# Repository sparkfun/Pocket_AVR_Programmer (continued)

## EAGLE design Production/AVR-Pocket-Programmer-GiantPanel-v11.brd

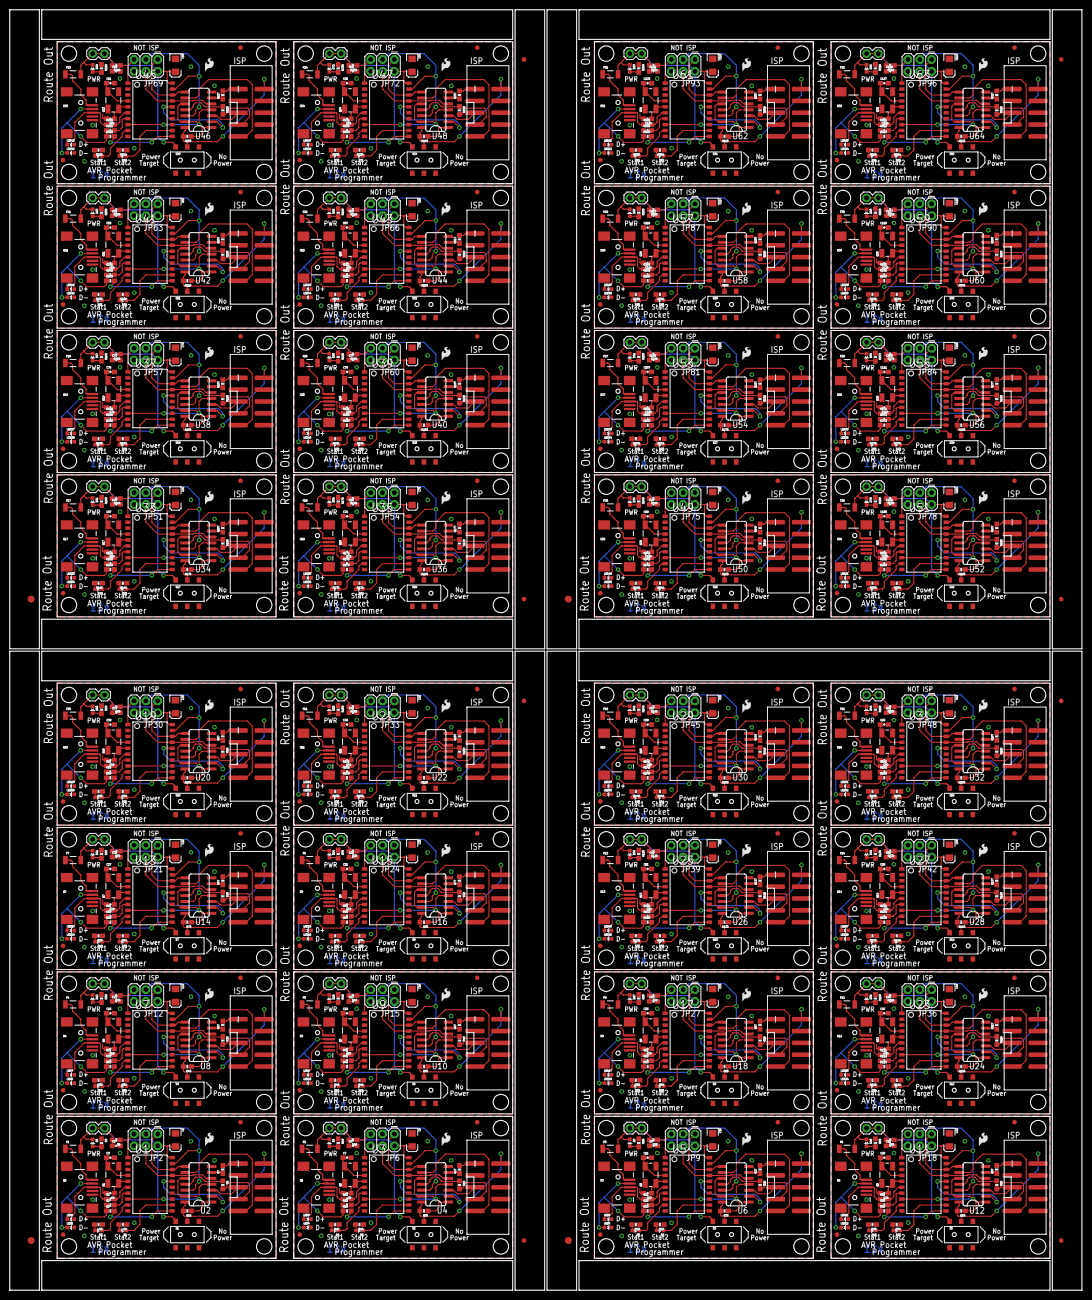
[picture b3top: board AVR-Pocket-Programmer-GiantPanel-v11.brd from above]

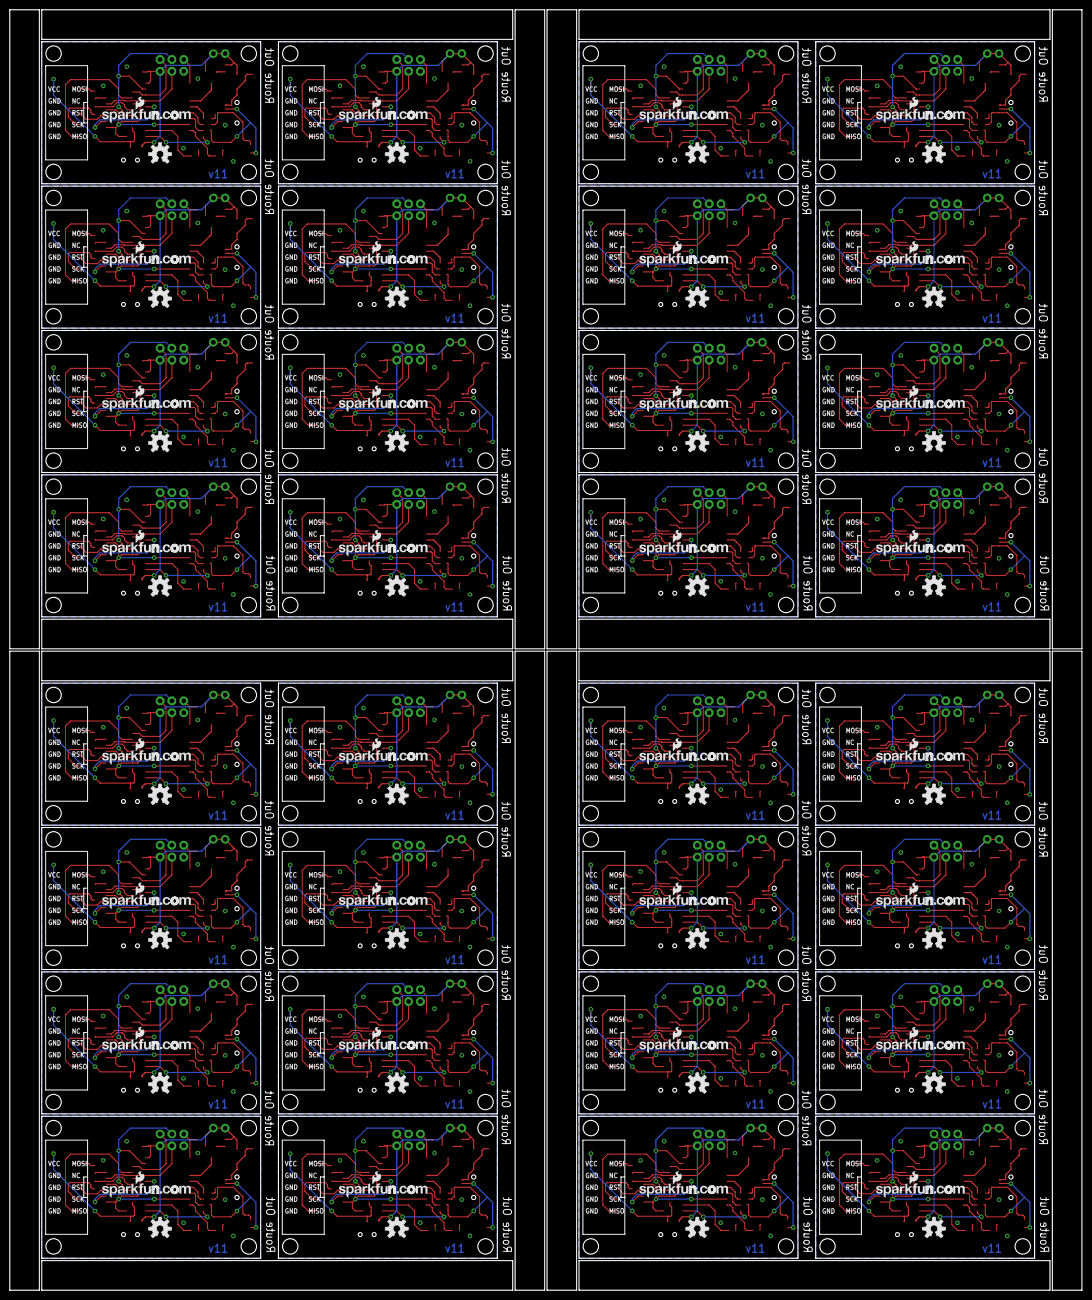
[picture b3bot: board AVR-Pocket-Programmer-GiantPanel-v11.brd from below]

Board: 2 copper layers, 230.1 x 274.8 mm, 1196 parts (64 on the bottom side), 896 nets.

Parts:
C1, C6, C10, C14, C18, C22, C26, C30, C34, C38, C42, C46, C50, C54, C58, C62, C66, C70, C74, C78, C82, C86, C90, C94, C98, C102, C106, C110, C114, C118, C122, C126: 10uF; EIA3216
C2, C5, C9, C13, C17, C21, C25, C29, C33, C37, C41, C45, C49, C53, C57, C61, C65, C69, C73, C77, C81, C85, C89, C93, C97, C101, C105, C109, C113, C117, C121, C125: 0.1uF; 0603-CAP
C3, C4, C7, C8, C11, C12, C15, C16, C19, C20, C23, C24, C27, C28, C31, C32, C35, C36, C39, C40, C43, C44, C47, C48, C51, C52, C55, C56, C59, C60, C63, C64, C67, C68, C71, C72, C75, C76, C79, C80, C83, C84, C87, C88, C91, C92, C95, C96, C99, C100, C103, C104, C107, C108, C111, C112, C115, C116, C119, C120, C123, C124, C127, C128: 22pF; 0603-CAP
D1, D3, D5, D6, D8, D9, D11, D12, D14, D15, D17, D18, D20, D21, D23, D24, D26, D27, D29, D30, D32, D33, D35, D36, D38, D39, D41, D42, D44, D45, D47, D48, D50, D51, D53, D54, D56, D57, D59, D60, D62, D63, D65, D66, D68, D69, D71, D72, D74, D75, D77, D78, D80, D81, D83, D84, D86, D87, D89, D90, D92, D93, D95, D96: Blue; LED-0603
D2, D4, D7, D10, D13, D16, D19, D22, D25, D28, D31, D34, D37, D40, D43, D46, D49, D52, D55, D58, D61, D64, D67, D70, D73, D76, D79, D82, D85, D88, D91, D94: Red; LED-0603
E$1, E$4, E$9, E$12: FIDUCIAL-1.5X3
E$2, E$3, E$5, E$6, E$7, E$8, E$10, E$11: FIDUCIAL-1X2
F1, F2, F3, F4, F5, F6, F7, F8, F9, F10, F11, F12, F13, F14, F15, F16, F17, F18, F19, F20, F21, F22, F23, F24, F25, F26, F27, F28, F29, F30, F31, F32: 500mA; PTC-1206-WIDE
JP1, JP4, JP7, JP10, JP13, JP16, JP19, JP22, JP25, JP28, JP31, JP34, JP37, JP40, JP43, JP46, JP49, JP52, JP55, JP58, JP61, JP64, JP67, JP70, JP73, JP76, JP79, JP82, JP85, JP88, JP91, JP94: Power Select; 1X02
JP2, JP6, JP9, JP12, JP15, JP18, JP21, JP24, JP27, JP30, JP33, JP36, JP39, JP42, JP45, JP48, JP51, JP54, JP57, JP60, JP63, JP66, JP69, JP72, JP75, JP78, JP81, JP84, JP87, JP90, JP93, JP96: AVR_SPI_PRG_6PTH; 2X3
JP3, JP5, JP8, JP11, JP14, JP17, JP20, JP23, JP26, JP29, JP32, JP35, JP38, JP41, JP44, JP47, JP50, JP53, JP56, JP59, JP62, JP65, JP68, JP71, JP74, JP77, JP80, JP83, JP86, JP89, JP92, JP95: AVR_SPI_PROG2SHROUDED_SMD; 2X5-SHROUDED_SMD
LED1, LED2, LED3, LED4, LED5, LED6, LED7, LED8, LED9, LED10, LED11, LED12, LED13, LED14, LED15, LED16, LED17, LED18, LED19, LED20, LED21, LED22, LED23, LED24, LED25, LED26, LED27, LED28, LED29, LED30, LED31, LED32, LED33, LED34, LED35, LED36, LED37, LED38, LED39, LED40, LED41, LED42, LED43, LED44, LED45, LED46, LED47, LED48, LED49, LED50, LED51, LED52, LED53, LED54, LED55, LED56, LED57, LED58, LED59, LED60, LED61, LED62, LED63, LED64: Blue; LED-0603
LOGO1, LOGO2, LOGO3, LOGO4, LOGO5, LOGO6, LOGO7, LOGO8, LOGO9, LOGO10, LOGO11, LOGO12, LOGO13, LOGO14, LOGO15, LOGO16, LOGO17, LOGO18, LOGO19, LOGO20, LOGO21, LOGO22, LOGO23, LOGO24, LOGO25, LOGO26, LOGO27, LOGO28, LOGO29, LOGO30, LOGO31, LOGO32: OSHW-LOGOM; OSHW-LOGO-M
Q1, Q2, Q3, Q4, Q5, Q6, Q7, Q8, Q9, Q10, Q11, Q12, Q13, Q14, Q15, Q16, Q17, Q18, Q19, Q20, Q21, Q22, Q23, Q24, Q25, Q26, Q27, Q28, Q29, Q30, Q31, Q32: 12 MHz; CRYSTAL-SMD-5X3
R1, R2, R11, R12, R21, R22, R31, R32, R41, R42, R51, R52, R61, R62, R71, R72, R81, R82, R91, R92, R101, R102, R111, R112, R121, R122, R131, R132, R141, R142, R151, R152, R161, R162, R171, R172, R181, R182, R191, R192, R201, R202, R211, R212, R221, R222, R231, R232, R241, R242, R251, R252, R261, R262, R271, R272, R281, R282, R291, R292, R301, R302, R311, R312: 27; 0603-RES
R3, R13, R23, R33, R43, R53, R63, R73, R83, R93, R103, R113, R123, R133, R143, R153, R163, R173, R183, R193, R203, R213, R223, R233, R243, R253, R263, R273, R283, R293, R303, R313: 1.5K; 0603-RES
R4, R5, R6, R9, R14, R15, R16, R19, R24, R25, R26, R29, R34, R35, R36, R39, R44, R45, R46, R49, R54, R55, R56, R59, R64, R65, R66, R69, R74, R75, R76, R79, R84, R85, R86, R89, R94, R95, R96, R99, R104, R105, R106, R109, R114, R115, R116, R119, R124, R125, R126, R129, R134, R135, R136, R139, R144, R145, R146, R149, R154, R155, R156, R159, R164, R165, R166, R169, R174, R175, R176, R179, R184, R185, R186, R189, R194, R195, R196, R199, R204, R205, R206, R209, R214, R215, R216, R219, R224, R225, R226, R229, R234, R235, R236, R239, R244, R245, R246, R249, R254, R255, R256, R259, R264, R265, R266, R269, R274, R275, R276, R279, R284, R285, R286, R289, R294, R295, R296, R299, R304, R305, R306, R309, R314, R315, R316, R319: 1K; 0603-RES
R7, R8, R17, R18, R27, R28, R37, R38, R47, R48, R57, R58, R67, R68, R77, R78, R87, R88, R97, R98, R107, R108, R117, R118, R127, R128, R137, R138, R147, R148, R157, R158, R167, R168, R177, R178, R187, R188, R197, R198, R207, R208, R217, R218, R227, R228, R237, R238, R247, R248, R257, R258, R267, R268, R277, R278, R287, R288, R297, R298, R307, R308, R317, R318: 100; 0603-RES
R10, R20, R30, R40, R50, R60, R70, R80, R90, R100, R110, R120, R130, R140, R150, R160, R170, R180, R190, R200, R210, R220, R230, R240, R250, R260, R270, R280, R290, R300, R310, R320: 22K; 0603-RES
S1, S2, S3, S4, S5, S6, S7, S8, S9, S10, S11, S12, S13, S14, S15, S16, S17, S18, S19, S20, S21, S22, S23, S24, S25, S26, S27, S28, S29, S30, S31, S32: Power Select; AYZ0202
U1, U3, U5, U7, U9, U11, U13, U15, U17, U19, U21, U23, U25, U27, U29, U31, U33, U35, U37, U39, U41, U43, U45, U47, U49, U51, U53, U55, U57, U59, U61, U63: ATTINY2313-20S; SO20L
U2, U4, U6, U8, U10, U12, U14, U16, U18, U20, U22, U24, U26, U28, U30, U32, U34, U36, U38, U40, U42, U44, U46, U48, U50, U52, U54, U56, U58, U60, U62, U64: 74ACT125D; SO014
U$1, U$3, U$4, U$5, U$9, U$10, U$11, U$12, U$17, U$18, U$19, U$20, U$25, U$26, U$27, U$28, U$33, U$34, U$35, U$36, U$41, U$42, U$43, U$44, U$49, U$50, U$51, U$52, U$57, U$58, U$59, U$60, U$65, U$66, U$67, U$68, U$73, U$74, U$75, U$76, U$81, U$82, U$83, U$84, U$89, U$90, U$91, U$92, U$97, U$98, U$99, U$100, U$105, U$106, U$107, U$108, U$113, U$114, U$115, U$116, U$121, U$122, U$123, U$124, U$129, U$130, U$131, U$132, U$137, U$138, U$139, U$140, U$145, U$146, U$147, U$148, U$153, U$154, U$155, U$156, U$161, U$162, U$163, U$164, U$169, U$170, U$171, U$172, U$177, U$178, U$179, U$180, U$185, U$186, U$187, U$188, U$193, U$194, U$195, U$196, U$201, U$202, U$203, U$204, U$209, U$210, U$211, U$212, U$217, U$218, U$219, U$220, U$225, U$226, U$227, U$228, U$233, U$234, U$235, U$236, U$241, U$242, U$243, U$244, U$249, U$250, U$251, U$252: STAND-OFF
U$2, U$16, U$24, U$32, U$40, U$48, U$56, U$64, U$72, U$80, U$88, U$96, U$104, U$112, U$120, U$128, U$136, U$144, U$152, U$160, U$168, U$176, U$184, U$192, U$200, U$208, U$216, U$224, U$232, U$240, U$248, U$256: LOGO-SFESK; SFE-LOGO-FLAME
U$6, U$7, U$13, U$14, U$21, U$22, U$29, U$30, U$37, U$38, U$45, U$46, U$53, U$54, U$61, U$62, U$69, U$70, U$77, U$78, U$85, U$86, U$93, U$94, U$101, U$102, U$109, U$110, U$117, U$118, U$125, U$126, U$133, U$134, U$141, U$142, U$149, U$150, U$157, U$158, U$165, U$166, U$173, U$174, U$181, U$182, U$189, U$190, U$197, U$198, U$205, U$206, U$213, U$214, U$221, U$222, U$229, U$230, U$237, U$238, U$245, U$246, U$253, U$254: FIDUCIAL1X2; FIDUCIAL-1X2
U$8, U$15, U$23, U$31, U$39, U$47, U$55, U$63, U$71, U$79, U$87, U$95, U$103, U$111, U$119, U$127, U$135, U$143, U$151, U$159, U$167, U$175, U$183, U$191, U$199, U$207, U$215, U$223, U$231, U$239, U$247, U$255: LOGO-SFENEW; SFE-NEW-WEBLOGO
X1, X2, X3, X4, X5, X6, X7, X8, X9, X10, X11, X12, X13, X14, X15, X16, X17, X18, X19, X20, X21, X22, X23, X24, X25, X26, X27, X28, X29, X30, X31, X32: USBSMD; USB-MINIB

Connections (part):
CTL: R10.1, U1.8, U2.1, U2.4, U2.10, U2.13
CTL1: R20.1, U3.8, U4.1, U4.4, U4.10, U4.13
CTL2: R30.1, U5.8, U6.1, U6.4, U6.10, U6.13
CTL3: R40.1, U7.8, U8.1, U8.4, U8.10, U8.13
CTL4: R50.1, U9.8, U10.1, U10.4, U10.10, U10.13
CTL5: R60.1, U11.8, U12.1, U12.4, U12.10, U12.13
CTL6: R70.1, U13.8, U14.1, U14.4, U14.10, U14.13
CTL7: R80.1, U15.8, U16.1, U16.4, U16.10, U16.13
CTL8: R90.1, U17.8, U18.1, U18.4, U18.10, U18.13
CTL9: R100.1, U19.8, U20.1, U20.4, U20.10, U20.13
CTL10: R110.1, U21.8, U22.1, U22.4, U22.10, U22.13
CTL11: R120.1, U23.8, U24.1, U24.4, U24.10, U24.13
CTL12: R130.1, U25.8, U26.1, U26.4, U26.10, U26.13
CTL13: R140.1, U27.8, U28.1, U28.4, U28.10, U28.13
CTL14: R150.1, U29.8, U30.1, U30.4, U30.10, U30.13
CTL15: R160.1, U31.8, U32.1, U32.4, U32.10, U32.13
CTL16: R170.1, U33.8, U34.1, U34.4, U34.10, U34.13
CTL17: R180.1, U35.8, U36.1, U36.4, U36.10, U36.13
CTL18: R190.1, U37.8, U38.1, U38.4, U38.10, U38.13
CTL19: R200.1, U39.8, U40.1, U40.4, U40.10, U40.13
CTL20: R210.1, U41.8, U42.1, U42.4, U42.10, U42.13
CTL21: R220.1, U43.8, U44.1, U44.4, U44.10, U44.13
CTL22: R230.1, U45.8, U46.1, U46.4, U46.10, U46.13
CTL23: R240.1, U47.8, U48.1, U48.4, U48.10, U48.13
CTL24: R250.1, U49.8, U50.1, U50.4, U50.10, U50.13
CTL25: R260.1, U51.8, U52.1, U52.4, U52.10, U52.13
CTL26: R270.1, U53.8, U54.1, U54.4, U54.10, U54.13
CTL27: R280.1, U55.8, U56.1, U56.4, U56.10, U56.13
CTL28: R290.1, U57.8, U58.1, U58.4, U58.10, U58.13
CTL29: R300.1, U59.8, U60.1, U60.4, U60.10, U60.13
CTL30: R310.1, U61.8, U62.1, U62.4, U62.10, U62.13
CTL31: R320.1, U63.8, U64.1, U64.4, U64.10, U64.13
D+: LED1.A, R1.1, X2.D+
D+1: LED3.A, R11.1, X1.D+
D+2: LED5.A, R21.1, X3.D+
D+3: LED7.A, R31.1, X4.D+
D+4: LED9.A, R41.1, X5.D+
D+5: LED11.A, R51.1, X6.D+
D+6: LED13.A, R61.1, X7.D+
D+7: LED15.A, R71.1, X8.D+
D+8: LED17.A, R81.1, X9.D+
D+9: LED19.A, R91.1, X10.D+
D+10: LED21.A, R101.1, X11.D+
D+11: LED23.A, R111.1, X12.D+
D+12: LED25.A, R121.1, X13.D+
D+13: LED27.A, R131.1, X14.D+
D+14: LED29.A, R141.1, X15.D+
D+15: LED31.A, R151.1, X16.D+
D+16: LED33.A, R161.1, X17.D+
D+17: LED35.A, R171.1, X18.D+
D+18: LED37.A, R181.1, X19.D+
D+19: LED39.A, R191.1, X20.D+
D+20: LED41.A, R201.1, X21.D+
D+21: LED43.A, R211.1, X22.D+
D+22: LED45.A, R221.1, X23.D+
D+23: LED47.A, R231.1, X24.D+
D+24: LED49.A, R241.1, X25.D+
D+25: LED51.A, R251.1, X26.D+
D+26: LED53.A, R261.1, X27.D+
D+27: LED55.A, R271.1, X28.D+
D+28: LED57.A, R281.1, X29.D+
D+29: LED59.A, R291.1, X30.D+
D+30: LED61.A, R301.1, X31.D+
D+31: LED63.A, R311.1, X32.D+
D-: LED2.A, R2.1, R3.1, X2.D-
D-1: LED4.A, R12.1, R13.1, X1.D-
D-2: LED6.A, R22.1, R23.1, X3.D-
D-3: LED8.A, R32.1, R33.1, X4.D-
D-4: LED10.A, R42.1, R43.1, X5.D-
D-5: LED12.A, R52.1, R53.1, X6.D-
D-6: LED14.A, R62.1, R63.1, X7.D-
D-7: LED16.A, R72.1, R73.1, X8.D-
D-8: LED18.A, R82.1, R83.1, X9.D-
D-9: LED20.A, R92.1, R93.1, X10.D-
D-10: LED22.A, R102.1, R103.1, X11.D-
D-11: LED24.A, R112.1, R113.1, X12.D-
D-12: LED26.A, R122.1, R123.1, X13.D-
D-13: LED28.A, R132.1, R133.1, X14.D-
D-14: LED30.A, R142.1, R143.1, X15.D-
D-15: LED32.A, R152.1, R153.1, X16.D-
D-16: LED34.A, R162.1, R163.1, X17.D-
D-17: LED36.A, R172.1, R173.1, X18.D-
D-18: LED38.A, R182.1, R183.1, X19.D-
D-19: LED40.A, R192.1, R193.1, X20.D-
D-20: LED42.A, R202.1, R203.1, X21.D-
D-21: LED44.A, R212.1, R213.1, X22.D-
D-22: LED46.A, R222.1, R223.1, X23.D-
D-23: LED48.A, R232.1, R233.1, X24.D-
D-24: LED50.A, R242.1, R243.1, X25.D-
D-25: LED52.A, R252.1, R253.1, X26.D-
D-26: LED54.A, R262.1, R263.1, X27.D-
D-27: LED56.A, R272.1, R273.1, X28.D-
D-28: LED58.A, R282.1, R283.1, X29.D-
D-29: LED60.A, R292.1, R293.1, X30.D-
D-30: LED62.A, R302.1, R303.1, X31.D-
D-31: LED64.A, R312.1, R313.1, X32.D-
GND: C1.C, C2.2, C3.2, C4.2, JP2.6, JP3.4, JP3.6, JP3.8, JP3.10, LED1.C, LED2.C, R4.1, R5.1, R9.1, U1.10, U2.7, X2.GND
GND1: C5.2, C6.C, C7.2, C8.2, JP5.4, JP5.6, JP5.8, JP5.10, JP6.6, LED3.C, LED4.C, R14.1, R15.1, R19.1, U3.10, U4.7, X1.GND
GND2: C9.2, C10.C, C11.2, C12.2, JP8.4, JP8.6, JP8.8, JP8.10, JP9.6, LED5.C, LED6.C, R24.1, R25.1, R29.1, U5.10, U6.7, X3.GND
GND3: C13.2, C14.C, C15.2, C16.2, JP11.4, JP11.6, JP11.8, JP11.10, JP12.6, LED7.C, LED8.C, R34.1, R35.1, R39.1, U7.10, U8.7, X4.GND
GND4: C17.2, C18.C, C19.2, C20.2, JP14.4, JP14.6, JP14.8, JP14.10, JP15.6, LED9.C, LED10.C, R44.1, R45.1, R49.1, U9.10, U10.7, X5.GND
GND5: C21.2, C22.C, C23.2, C24.2, JP17.4, JP17.6, JP17.8, JP17.10, JP18.6, LED11.C, LED12.C, R54.1, R55.1, R59.1, U11.10, U12.7, X6.GND
GND6: C25.2, C26.C, C27.2, C28.2, JP20.4, JP20.6, JP20.8, JP20.10, JP21.6, LED13.C, LED14.C, R64.1, R65.1, R69.1, U13.10, U14.7, X7.GND
GND7: C29.2, C30.C, C31.2, C32.2, JP23.4, JP23.6, JP23.8, JP23.10, JP24.6, LED15.C, LED16.C, R74.1, R75.1, R79.1, U15.10, U16.7, X8.GND
GND8: C33.2, C34.C, C35.2, C36.2, JP26.4, JP26.6, JP26.8, JP26.10, JP27.6, LED17.C, LED18.C, R84.1, R85.1, R89.1, U17.10, U18.7, X9.GND
GND9: C37.2, C38.C, C39.2, C40.2, JP29.4, JP29.6, JP29.8, JP29.10, JP30.6, LED19.C, LED20.C, R94.1, R95.1, R99.1, U19.10, U20.7, X10.GND
GND10: C41.2, C42.C, C43.2, C44.2, JP32.4, JP32.6, JP32.8, JP32.10, JP33.6, LED21.C, LED22.C, R104.1, R105.1, R109.1, U21.10, U22.7, X11.GND
GND11: C45.2, C46.C, C47.2, C48.2, JP35.4, JP35.6, JP35.8, JP35.10, JP36.6, LED23.C, LED24.C, R114.1, R115.1, R119.1, U23.10, U24.7, X12.GND
GND12: C49.2, C50.C, C51.2, C52.2, JP38.4, JP38.6, JP38.8, JP38.10, JP39.6, LED25.C, LED26.C, R124.1, R125.1, R129.1, U25.10, U26.7, X13.GND
GND13: C53.2, C54.C, C55.2, C56.2, JP41.4, JP41.6, JP41.8, JP41.10, JP42.6, LED27.C, LED28.C, R134.1, R135.1, R139.1, U27.10, U28.7, X14.GND
GND14: C57.2, C58.C, C59.2, C60.2, JP44.4, JP44.6, JP44.8, JP44.10, JP45.6, LED29.C, LED30.C, R144.1, R145.1, R149.1, U29.10, U30.7, X15.GND
GND15: C61.2, C62.C, C63.2, C64.2, JP47.4, JP47.6, JP47.8, JP47.10, JP48.6, LED31.C, LED32.C, R154.1, R155.1, R159.1, U31.10, U32.7, X16.GND
GND16: C65.2, C66.C, C67.2, C68.2, JP50.4, JP50.6, JP50.8, JP50.10, JP51.6, LED33.C, LED34.C, R164.1, R165.1, R169.1, U33.10, U34.7, X17.GND
GND17: C69.2, C70.C, C71.2, C72.2, JP53.4, JP53.6, JP53.8, JP53.10, JP54.6, LED35.C, LED36.C, R174.1, R175.1, R179.1, U35.10, U36.7, X18.GND
GND18: C73.2, C74.C, C75.2, C76.2, JP56.4, JP56.6, JP56.8, JP56.10, JP57.6, LED37.C, LED38.C, R184.1, R185.1, R189.1, U37.10, U38.7, X19.GND
GND19: C77.2, C78.C, C79.2, C80.2, JP59.4, JP59.6, JP59.8, JP59.10, JP60.6, LED39.C, LED40.C, R194.1, R195.1, R199.1, U39.10, U40.7, X20.GND
GND20: C81.2, C82.C, C83.2, C84.2, JP62.4, JP62.6, JP62.8, JP62.10, JP63.6, LED41.C, LED42.C, R204.1, R205.1, R209.1, U41.10, U42.7, X21.GND
GND21: C85.2, C86.C, C87.2, C88.2, JP65.4, JP65.6, JP65.8, JP65.10, JP66.6, LED43.C, LED44.C, R214.1, R215.1, R219.1, U43.10, U44.7, X22.GND
GND22: C89.2, C90.C, C91.2, C92.2, JP68.4, JP68.6, JP68.8, JP68.10, JP69.6, LED45.C, LED46.C, R224.1, R225.1, R229.1, U45.10, U46.7, X23.GND
GND23: C93.2, C94.C, C95.2, C96.2, JP71.4, JP71.6, JP71.8, JP71.10, JP72.6, LED47.C, LED48.C, R234.1, R235.1, R239.1, U47.10, U48.7, X24.GND
GND24: C97.2, C98.C, C99.2, C100.2, JP74.4, JP74.6, JP74.8, JP74.10, JP75.6, LED49.C, LED50.C, R244.1, R245.1, R249.1, U49.10, U50.7, X25.GND
GND25: C101.2, C102.C, C103.2, C104.2, JP77.4, JP77.6, JP77.8, JP77.10, JP78.6, LED51.C, LED52.C, R254.1, R255.1, R259.1, U51.10, U52.7, X26.GND
GND26: C105.2, C106.C, C107.2, C108.2, JP80.4, JP80.6, JP80.8, JP80.10, JP81.6, LED53.C, LED54.C, R264.1, R265.1, R269.1, U53.10, U54.7, X27.GND
GND27: C109.2, C110.C, C111.2, C112.2, JP83.4, JP83.6, JP83.8, JP83.10, JP84.6, LED55.C, LED56.C, R274.1, R275.1, R279.1, U55.10, U56.7, X28.GND
GND28: C113.2, C114.C, C115.2, C116.2, JP86.4, JP86.6, JP86.8, JP86.10, JP87.6, LED57.C, LED58.C, R284.1, R285.1, R289.1, U57.10, U58.7, X29.GND
GND29: C117.2, C118.C, C119.2, C120.2, JP89.4, JP89.6, JP89.8, JP89.10, JP90.6, LED59.C, LED60.C, R294.1, R295.1, R299.1, U59.10, U60.7, X30.GND
GND30: C121.2, C122.C, C123.2, C124.2, JP92.4, JP92.6, JP92.8, JP92.10, JP93.6, LED61.C, LED62.C, R304.1, R305.1, R309.1, U61.10, U62.7, X31.GND
GND31: C125.2, C126.C, C127.2, C128.2, JP95.4, JP95.6, JP95.8, JP95.10, JP96.6, LED63.C, LED64.C, R314.1, R315.1, R319.1, U63.10, U64.7, X32.GND
MISO': JP2.1, U1.18, U2.8
MISO'1: JP6.1, U3.18, U4.8
MISO'2: JP9.1, U5.18, U6.8
MISO'3: JP12.1, U7.18, U8.8
MISO'4: JP15.1, U9.18, U10.8
MISO'5: JP18.1, U11.18, U12.8
MISO'6: JP21.1, U13.18, U14.8
MISO'7: JP24.1, U15.18, U16.8
MISO'8: JP27.1, U17.18, U18.8
MISO'9: JP30.1, U19.18, U20.8
MISO'10: JP33.1, U21.18, U22.8
MISO'11: JP36.1, U23.18, U24.8
MISO'12: JP39.1, U25.18, U26.8
MISO'13: JP42.1, U27.18, U28.8
MISO'14: JP45.1, U29.18, U30.8
MISO'15: JP48.1, U31.18, U32.8
MISO'16: JP51.1, U33.18, U34.8
MISO'17: JP54.1, U35.18, U36.8
MISO'18: JP57.1, U37.18, U38.8
MISO'19: JP60.1, U39.18, U40.8
MISO'20: JP63.1, U41.18, U42.8
MISO'21: JP66.1, U43.18, U44.8
MISO'22: JP69.1, U45.18, U46.8
MISO'23: JP72.1, U47.18, U48.8
MISO'24: JP75.1, U49.18, U50.8
MISO'25: JP78.1, U51.18, U52.8
MISO'26: JP81.1, U53.18, U54.8
MISO'27: JP84.1, U55.18, U56.8
MISO'28: JP87.1, U57.18, U58.8
MISO'29: JP90.1, U59.18, U60.8
MISO'30: JP93.1, U61.18, U62.8
MISO'31: JP96.1, U63.18, U64.8
MOSI': JP2.4, U1.17, U2.5
MOSI'1: JP6.4, U3.17, U4.5
MOSI'2: JP9.4, U5.17, U6.5
MOSI'3: JP12.4, U7.17, U8.5
MOSI'4: JP15.4, U9.17, U10.5
MOSI'5: JP18.4, U11.17, U12.5
MOSI'6: JP21.4, U13.17, U14.5
MOSI'7: JP24.4, U15.17, U16.5
MOSI'8: JP27.4, U17.17, U18.5
MOSI'9: JP30.4, U19.17, U20.5
MOSI'10: JP33.4, U21.17, U22.5
MOSI'11: JP36.4, U23.17, U24.5
MOSI'12: JP39.4, U25.17, U26.5
MOSI'13: JP42.4, U27.17, U28.5
MOSI'14: JP45.4, U29.17, U30.5
MOSI'15: JP48.4, U31.17, U32.5
MOSI'16: JP51.4, U33.17, U34.5
MOSI'17: JP54.4, U35.17, U36.5
MOSI'18: JP57.4, U37.17, U38.5
MOSI'19: JP60.4, U39.17, U40.5
MOSI'20: JP63.4, U41.17, U42.5
MOSI'21: JP66.4, U43.17, U44.5
MOSI'22: JP69.4, U45.17, U46.5
MOSI'23: JP72.4, U47.17, U48.5
MOSI'24: JP75.4, U49.17, U50.5
MOSI'25: JP78.4, U51.17, U52.5
MOSI'26: JP81.4, U53.17, U54.5
MOSI'27: JP84.4, U55.17, U56.5
MOSI'28: JP87.4, U57.17, U58.5
MOSI'29: JP90.4, U59.17, U60.5
MOSI'30: JP93.4, U61.17, U62.5
MOSI'31: JP96.4, U63.17, U64.5
unnamed: R3.2, U1.11
unnamed: D2.A, U1.9
unnamed: D3.C, R9.2
unnamed: F1.1, X2.VBUS
unnamed: C3.1, Q1.3, U1.4
unnamed: C4.1, Q1.1, U1.5
unnamed: R13.2, U3.11
unnamed: D4.A, U3.9
unnamed: D5.A, U3.12
unnamed: D5.C, R14.2
unnamed: D4.C, R15.2
unnamed: R17.1, U4.6
unnamed: R18.1, U4.11
unnamed: D6.C, R19.2
unnamed: F2.1, X1.VBUS
unnamed: C7.1, Q2.3, U3.4
unnamed: D1.A, U1.12
unnamed: D1.C, R4.2
unnamed: D2.C, R5.2
unnamed: C8.1, Q2.1, U3.5
unnamed: R23.2, U5.11
unnamed: R7.1, U2.6
unnamed: D7.A, U5.9
unnamed: D8.A, U5.12
unnamed: R8.1, U2.11
unnamed: D8.C, R24.2
unnamed: D7.C, R25.2
unnamed: R27.1, U6.6
unnamed: R28.1, U6.11
unnamed: D9.C, R29.2
unnamed: F3.1, X3.VBUS
unnamed: C11.1, Q3.3, U5.4
unnamed: C12.1, Q3.1, U5.5
unnamed: R33.2, U7.11
unnamed: D10.A, U7.9
unnamed: D11.A, U7.12
unnamed: D11.C, R34.2
unnamed: D10.C, R35.2
unnamed: R37.1, U8.6
unnamed: R38.1, U8.11
unnamed: D12.C, R39.2
unnamed: F4.1, X4.VBUS
unnamed: C15.1, Q4.3, U7.4
unnamed: C16.1, Q4.1, U7.5
unnamed: R43.2, U9.11
unnamed: D13.A, U9.9
unnamed: D14.A, U9.12
unnamed: D14.C, R44.2
unnamed: D13.C, R45.2
unnamed: R47.1, U10.6
unnamed: R48.1, U10.11
unnamed: D15.C, R49.2
unnamed: F5.1, X5.VBUS
unnamed: C19.1, Q5.3, U9.4
unnamed: C20.1, Q5.1, U9.5
unnamed: R53.2, U11.11
unnamed: D16.A, U11.9
unnamed: D17.A, U11.12
unnamed: D17.C, R54.2
unnamed: D16.C, R55.2
unnamed: R57.1, U12.6
unnamed: R58.1, U12.11
unnamed: D18.C, R59.2
unnamed: F6.1, X6.VBUS
unnamed: C23.1, Q6.3, U11.4
unnamed: C24.1, Q6.1, U11.5
unnamed: R63.2, U13.11
unnamed: D19.A, U13.9
unnamed: D20.A, U13.12
unnamed: D20.C, R64.2
unnamed: D19.C, R65.2
unnamed: R67.1, U14.6
unnamed: R68.1, U14.11
unnamed: D21.C, R69.2
unnamed: F7.1, X7.VBUS
unnamed: C27.1, Q7.3, U13.4
unnamed: C28.1, Q7.1, U13.5
unnamed: R73.2, U15.11
unnamed: D22.A, U15.9
unnamed: D23.A, U15.12
unnamed: D23.C, R74.2
unnamed: D22.C, R75.2
unnamed: R77.1, U16.6
unnamed: R78.1, U16.11
unnamed: D24.C, R79.2
unnamed: F8.1, X8.VBUS
unnamed: C31.1, Q8.3, U15.4
unnamed: C32.1, Q8.1, U15.5
unnamed: R83.2, U17.11
unnamed: D25.A, U17.9
unnamed: D26.A, U17.12
unnamed: D26.C, R84.2
unnamed: D25.C, R85.2
unnamed: R87.1, U18.6
unnamed: R88.1, U18.11
unnamed: D27.C, R89.2
unnamed: F9.1, X9.VBUS
unnamed: C35.1, Q9.3, U17.4
unnamed: C36.1, Q9.1, U17.5
unnamed: R93.2, U19.11
unnamed: D28.A, U19.9
unnamed: D29.A, U19.12
unnamed: D29.C, R94.2
unnamed: D28.C, R95.2
unnamed: R97.1, U20.6
unnamed: R98.1, U20.11
unnamed: D30.C, R99.2
unnamed: F10.1, X10.VBUS
unnamed: C39.1, Q10.3, U19.4
unnamed: C40.1, Q10.1, U19.5
unnamed: R103.2, U21.11
unnamed: D31.A, U21.9
unnamed: D32.A, U21.12
unnamed: D32.C, R104.2
unnamed: D31.C, R105.2
unnamed: R107.1, U22.6
unnamed: R108.1, U22.11
unnamed: D33.C, R109.2
unnamed: F11.1, X11.VBUS
unnamed: C43.1, Q11.3, U21.4
unnamed: C44.1, Q11.1, U21.5
unnamed: R113.2, U23.11
unnamed: D34.A, U23.9
unnamed: D35.A, U23.12
unnamed: D35.C, R114.2
unnamed: D34.C, R115.2
unnamed: R117.1, U24.6
unnamed: R118.1, U24.11
unnamed: D36.C, R119.2
unnamed: F12.1, X12.VBUS
unnamed: C47.1, Q12.3, U23.4
unnamed: C48.1, Q12.1, U23.5
unnamed: R123.2, U25.11
unnamed: D37.A, U25.9
unnamed: D38.A, U25.12
unnamed: D38.C, R124.2
unnamed: D37.C, R125.2
unnamed: R127.1, U26.6
unnamed: R128.1, U26.11
unnamed: D39.C, R129.2
unnamed: F13.1, X13.VBUS
unnamed: C51.1, Q13.3, U25.4
unnamed: C52.1, Q13.1, U25.5
unnamed: R133.2, U27.11
unnamed: D40.A, U27.9
unnamed: D41.A, U27.12
unnamed: D41.C, R134.2
unnamed: D40.C, R135.2
unnamed: R137.1, U28.6
unnamed: R138.1, U28.11
unnamed: D42.C, R139.2
unnamed: F14.1, X14.VBUS
unnamed: C55.1, Q14.3, U27.4
unnamed: C56.1, Q14.1, U27.5
unnamed: R143.2, U29.11
unnamed: D43.A, U29.9
unnamed: D44.A, U29.12
unnamed: D44.C, R144.2
unnamed: D43.C, R145.2
unnamed: R147.1, U30.6
unnamed: R148.1, U30.11
unnamed: D45.C, R149.2
unnamed: F15.1, X15.VBUS
unnamed: C59.1, Q15.3, U29.4
unnamed: C60.1, Q15.1, U29.5
unnamed: R153.2, U31.11
unnamed: D46.A, U31.9
unnamed: D47.A, U31.12
unnamed: D47.C, R154.2
unnamed: D46.C, R155.2
unnamed: R157.1, U32.6
unnamed: R158.1, U32.11
unnamed: D48.C, R159.2
unnamed: F16.1, X16.VBUS
unnamed: C63.1, Q16.3, U31.4
unnamed: C64.1, Q16.1, U31.5
unnamed: R163.2, U33.11
unnamed: D49.A, U33.9
unnamed: D50.A, U33.12
unnamed: D50.C, R164.2
unnamed: D49.C, R165.2
unnamed: R167.1, U34.6
unnamed: R168.1, U34.11
unnamed: D51.C, R169.2
unnamed: F17.1, X17.VBUS
unnamed: C67.1, Q17.3, U33.4
unnamed: C68.1, Q17.1, U33.5
unnamed: R173.2, U35.11
unnamed: D52.A, U35.9
unnamed: D53.A, U35.12
unnamed: D53.C, R174.2
unnamed: D52.C, R175.2
unnamed: R177.1, U36.6
unnamed: R178.1, U36.11
unnamed: D54.C, R179.2
unnamed: F18.1, X18.VBUS
unnamed: C71.1, Q18.3, U35.4
unnamed: C72.1, Q18.1, U35.5
unnamed: R183.2, U37.11
unnamed: D55.A, U37.9
unnamed: D56.A, U37.12
unnamed: D56.C, R184.2
unnamed: D55.C, R185.2
unnamed: R187.1, U38.6
unnamed: R188.1, U38.11
unnamed: D57.C, R189.2
unnamed: F19.1, X19.VBUS
unnamed: C75.1, Q19.3, U37.4
unnamed: C76.1, Q19.1, U37.5
unnamed: R193.2, U39.11
unnamed: D58.A, U39.9
unnamed: D59.A, U39.12
unnamed: D59.C, R194.2
unnamed: D58.C, R195.2
unnamed: R197.1, U40.6
unnamed: R198.1, U40.11
unnamed: D60.C, R199.2
unnamed: F20.1, X20.VBUS
unnamed: C79.1, Q20.3, U39.4
unnamed: C80.1, Q20.1, U39.5
unnamed: R203.2, U41.11
unnamed: D61.A, U41.9
unnamed: D62.A, U41.12
unnamed: D62.C, R204.2
unnamed: D61.C, R205.2
unnamed: R207.1, U42.6
unnamed: R208.1, U42.11
unnamed: D63.C, R209.2
unnamed: F21.1, X21.VBUS
unnamed: C83.1, Q21.3, U41.4
unnamed: C84.1, Q21.1, U41.5
unnamed: R213.2, U43.11
unnamed: D64.A, U43.9
unnamed: D65.A, U43.12
unnamed: D65.C, R214.2
unnamed: D64.C, R215.2
unnamed: R217.1, U44.6
unnamed: R218.1, U44.11
unnamed: D66.C, R219.2
unnamed: F22.1, X22.VBUS
unnamed: C87.1, Q22.3, U43.4
unnamed: C88.1, Q22.1, U43.5
unnamed: R223.2, U45.11
unnamed: D67.A, U45.9
unnamed: D68.A, U45.12
unnamed: D68.C, R224.2
unnamed: D67.C, R225.2
unnamed: R227.1, U46.6
unnamed: R228.1, U46.11
unnamed: D69.C, R229.2
unnamed: F23.1, X23.VBUS
unnamed: C91.1, Q23.3, U45.4
unnamed: C92.1, Q23.1, U45.5
unnamed: R233.2, U47.11
unnamed: D70.A, U47.9
unnamed: D71.A, U47.12
unnamed: D71.C, R234.2
unnamed: D70.C, R235.2
unnamed: R237.1, U48.6
unnamed: R238.1, U48.11
unnamed: D72.C, R239.2
unnamed: F24.1, X24.VBUS
unnamed: C95.1, Q24.3, U47.4
unnamed: C96.1, Q24.1, U47.5
unnamed: R243.2, U49.11
unnamed: D73.A, U49.9
unnamed: D74.A, U49.12
unnamed: D74.C, R244.2
unnamed: D73.C, R245.2
unnamed: R247.1, U50.6
unnamed: R248.1, U50.11
unnamed: D75.C, R249.2
unnamed: F25.1, X25.VBUS
unnamed: C99.1, Q25.3, U49.4
unnamed: C100.1, Q25.1, U49.5
unnamed: R253.2, U51.11
unnamed: D76.A, U51.9
unnamed: D77.A, U51.12
unnamed: D77.C, R254.2
unnamed: D76.C, R255.2
unnamed: R257.1, U52.6
unnamed: R258.1, U52.11
unnamed: D78.C, R259.2
unnamed: F26.1, X26.VBUS
unnamed: C103.1, Q26.3, U51.4
unnamed: C104.1, Q26.1, U51.5
unnamed: R263.2, U53.11
unnamed: D79.A, U53.9
unnamed: D80.A, U53.12
unnamed: D80.C, R264.2
unnamed: D79.C, R265.2
unnamed: R267.1, U54.6
unnamed: R268.1, U54.11
unnamed: D81.C, R269.2
unnamed: F27.1, X27.VBUS
unnamed: C107.1, Q27.3, U53.4
unnamed: C108.1, Q27.1, U53.5
unnamed: R273.2, U55.11
unnamed: D82.A, U55.9
unnamed: D83.A, U55.12
unnamed: D83.C, R274.2
unnamed: D82.C, R275.2
unnamed: R277.1, U56.6
unnamed: R278.1, U56.11
unnamed: D84.C, R279.2
unnamed: F28.1, X28.VBUS
unnamed: C111.1, Q28.3, U55.4
unnamed: C112.1, Q28.1, U55.5
unnamed: R283.2, U57.11
unnamed: D85.A, U57.9
unnamed: D86.A, U57.12
unnamed: D86.C, R284.2
unnamed: D85.C, R285.2
unnamed: R287.1, U58.6
unnamed: R288.1, U58.11
unnamed: D87.C, R289.2
unnamed: F29.1, X29.VBUS
unnamed: C115.1, Q29.3, U57.4
unnamed: C116.1, Q29.1, U57.5
unnamed: R293.2, U59.11
unnamed: D88.A, U59.9
unnamed: D89.A, U59.12
unnamed: D89.C, R294.2
unnamed: D88.C, R295.2
unnamed: R297.1, U60.6
unnamed: R298.1, U60.11
unnamed: D90.C, R299.2
unnamed: F30.1, X30.VBUS
unnamed: C119.1, Q30.3, U59.4
unnamed: C120.1, Q30.1, U59.5
unnamed: R303.2, U61.11
unnamed: D91.A, U61.9
unnamed: D92.A, U61.12
unnamed: D92.C, R304.2
unnamed: D91.C, R305.2
unnamed: R307.1, U62.6
unnamed: R308.1, U62.11
unnamed: D93.C, R309.2
unnamed: F31.1, X31.VBUS
unnamed: C123.1, Q31.3, U61.4
unnamed: C124.1, Q31.1, U61.5
unnamed: R313.2, U63.11
unnamed: D94.A, U63.9
unnamed: D95.A, U63.12
unnamed: D95.C, R314.2
unnamed: D94.C, R315.2
unnamed: R317.1, U64.6
unnamed: R318.1, U64.11
unnamed: D96.C, R319.2
unnamed: F32.1, X32.VBUS
unnamed: C127.1, Q32.3, U63.4
unnamed: C128.1, Q32.1, U63.5
PD+: R1.2, U1.6
PD+1: R11.2, U3.6
PD+2: R21.2, U5.6
PD+3: R31.2, U7.6
PD+4: R41.2, U9.6
PD+5: R51.2, U11.6
PD+6: R61.2, U13.6
PD+7: R71.2, U15.6
PD+8: R81.2, U17.6
PD+9: R91.2, U19.6
PD+10: R101.2, U21.6
PD+11: R111.2, U23.6
PD+12: R121.2, U25.6
PD+13: R131.2, U27.6
PD+14: R141.2, U29.6
PD+15: R151.2, U31.6
PD+16: R161.2, U33.6
PD+17: R171.2, U35.6
PD+18: R181.2, U37.6
PD+19: R191.2, U39.6
PD+20: R201.2, U41.6
PD+21: R211.2, U43.6
PD+22: R221.2, U45.6
PD+23: R231.2, U47.6
PD+24: R241.2, U49.6
PD+25: R251.2, U51.6
PD+26: R261.2, U53.6
PD+27: R271.2, U55.6
PD+28: R281.2, U57.6
PD+29: R291.2, U59.6
PD+30: R301.2, U61.6
PD+31: R311.2, U63.6
PD-: R2.2, U1.7
PD-1: R12.2, U3.7
PD-2: R22.2, U5.7
PD-3: R32.2, U7.7
PD-4: R42.2, U9.7
PD-5: R52.2, U11.7
PD-6: R62.2, U13.7
PD-7: R72.2, U15.7
PD-8: R82.2, U17.7
PD-9: R92.2, U19.7
PD-10: R102.2, U21.7
PD-11: R112.2, U23.7
PD-12: R122.2, U25.7
PD-13: R132.2, U27.7
PD-14: R142.2, U29.7
PD-15: R152.2, U31.7
PD-16: R162.2, U33.7
PD-17: R172.2, U35.7
PD-18: R182.2, U37.7
PD-19: R192.2, U39.7
PD-20: R202.2, U41.7
PD-21: R212.2, U43.7
PD-22: R222.2, U45.7
PD-23: R232.2, U47.7
PD-24: R242.2, U49.7
PD-25: R252.2, U51.7
PD-26: R262.2, U53.7
PD-27: R272.2, U55.7
PD-28: R282.2, U57.7
PD-29: R292.2, U59.7
PD-30: R302.2, U61.7
PD-31: R312.2, U63.7
RST: JP2.5, R6.1, U1.1
RST1: JP6.5, R16.1, U3.1
RST2: JP9.5, R26.1, U5.1
RST3: JP12.5, R36.1, U7.1
RST4: JP15.5, R46.1, U9.1
RST5: JP18.5, R56.1, U11.1
RST6: JP21.5, R66.1, U13.1
RST7: JP24.5, R76.1, U15.1
RST8: JP27.5, R86.1, U17.1
RST9: JP30.5, R96.1, U19.1
RST10: JP33.5, R106.1, U21.1
RST11: JP36.5, R116.1, U23.1
RST12: JP39.5, R126.1, U25.1
RST13: JP42.5, R136.1, U27.1
RST14: JP45.5, R146.1, U29.1
RST15: JP48.5, R156.1, U31.1
RST16: JP51.5, R166.1, U33.1
RST17: JP54.5, R176.1, U35.1
RST18: JP57.5, R186.1, U37.1
RST19: JP60.5, R196.1, U39.1
RST20: JP63.5, R206.1, U41.1
RST21: JP66.5, R216.1, U43.1
RST22: JP69.5, R226.1, U45.1
RST23: JP72.5, R236.1, U47.1
RST24: JP75.5, R246.1, U49.1
RST25: JP78.5, R256.1, U51.1
RST26: JP81.5, R266.1, U53.1
RST27: JP84.5, R276.1, U55.1
RST28: JP87.5, R286.1, U57.1
RST29: JP90.5, R296.1, U59.1
RST30: JP93.5, R306.1, U61.1
RST31: JP96.5, R316.1, U63.1
RST': U1.16, U2.2
RST'1: U3.16, U4.2
RST'2: U5.16, U6.2
RST'3: U7.16, U8.2
RST'4: U9.16, U10.2
RST'5: U11.16, U12.2
RST'6: U13.16, U14.2
RST'7: U15.16, U16.2
RST'8: U17.16, U18.2
RST'9: U19.16, U20.2
RST'10: U21.16, U22.2
RST'11: U23.16, U24.2
RST'12: U25.16, U26.2
RST'13: U27.16, U28.2
RST'14: U29.16, U30.2
RST'15: U31.16, U32.2
RST'16: U33.16, U34.2
RST'17: U35.16, U36.2
RST'18: U37.16, U38.2
RST'19: U39.16, U40.2
RST'20: U41.16, U42.2
RST'21: U43.16, U44.2
RST'22: U45.16, U46.2
RST'23: U47.16, U48.2
RST'24: U49.16, U50.2
RST'25: U51.16, U52.2
RST'26: U53.16, U54.2
RST'27: U55.16, U56.2
RST'28: U57.16, U58.2
RST'29: U59.16, U60.2
RST'30: U61.16, U62.2
RST'31: U63.16, U64.2
SCK': JP2.3, U1.19, U2.12
SCK'1: JP6.3, U3.19, U4.12
SCK'2: JP9.3, U5.19, U6.12
SCK'3: JP12.3, U7.19, U8.12
SCK'4: JP15.3, U9.19, U10.12
SCK'5: JP18.3, U11.19, U12.12
SCK'6: JP21.3, U13.19, U14.12
SCK'7: JP24.3, U15.19, U16.12
SCK'8: JP27.3, U17.19, U18.12
SCK'9: JP30.3, U19.19, U20.12
SCK'10: JP33.3, U21.19, U22.12
SCK'11: JP36.3, U23.19, U24.12
SCK'12: JP39.3, U25.19, U26.12
SCK'13: JP42.3, U27.19, U28.12
SCK'14: JP45.3, U29.19, U30.12
SCK'15: JP48.3, U31.19, U32.12
SCK'16: JP51.3, U33.19, U34.12
SCK'17: JP54.3, U35.19, U36.12
SCK'18: JP57.3, U37.19, U38.12
SCK'19: JP60.3, U39.19, U40.12
SCK'20: JP63.3, U41.19, U42.12
SCK'21: JP66.3, U43.19, U44.12
SCK'22: JP69.3, U45.19, U46.12
SCK'23: JP72.3, U47.19, U48.12
SCK'24: JP75.3, U49.19, U50.12
SCK'25: JP78.3, U51.19, U52.12
SCK'26: JP81.3, U53.19, U54.12
SCK'27: JP84.3, U55.19, U56.12
SCK'28: JP87.3, U57.19, U58.12
SCK'29: JP90.3, U59.19, U60.12
SCK'30: JP93.3, U61.19, U62.12
SCK'31: JP96.3, U63.19, U64.12
TARGET-MISO: JP3.9, U2.9
TARGET-MISO1: JP5.9, U4.9
TARGET-MISO2: JP8.9, U6.9
TARGET-MISO3: JP11.9, U8.9
TARGET-MISO4: JP14.9, U10.9
TARGET-MISO5: JP17.9, U12.9
TARGET-MISO6: JP20.9, U14.9
TARGET-MISO7: JP23.9, U16.9
TARGET-MISO8: JP26.9, U18.9
TARGET-MISO9: JP29.9, U20.9
TARGET-MISO10: JP32.9, U22.9
TARGET-MISO11: JP35.9, U24.9
TARGET-MISO12: JP38.9, U26.9
TARGET-MISO13: JP41.9, U28.9
TARGET-MISO14: JP44.9, U30.9
TARGET-MISO15: JP47.9, U32.9
TARGET-MISO16: JP50.9, U34.9
TARGET-MISO17: JP53.9, U36.9
TARGET-MISO18: JP56.9, U38.9
TARGET-MISO19: JP59.9, U40.9
TARGET-MISO20: JP62.9, U42.9
TARGET-MISO21: JP65.9, U44.9
TARGET-MISO22: JP68.9, U46.9
TARGET-MISO23: JP71.9, U48.9
TARGET-MISO24: JP74.9, U50.9
TARGET-MISO25: JP77.9, U52.9
TARGET-MISO26: JP80.9, U54.9
TARGET-MISO27: JP83.9, U56.9
TARGET-MISO28: JP86.9, U58.9
TARGET-MISO29: JP89.9, U60.9
TARGET-MISO30: JP92.9, U62.9
TARGET-MISO31: JP95.9, U64.9
TARGET-MOSI: JP3.1, R7.2
TARGET-MOSI1: JP5.1, R17.2
TARGET-MOSI2: JP8.1, R27.2
TARGET-MOSI3: JP11.1, R37.2
TARGET-MOSI4: JP14.1, R47.2
TARGET-MOSI5: JP17.1, R57.2
TARGET-MOSI6: JP20.1, R67.2
TARGET-MOSI7: JP23.1, R77.2
TARGET-MOSI8: JP26.1, R87.2
TARGET-MOSI9: JP29.1, R97.2
TARGET-MOSI10: JP32.1, R107.2
TARGET-MOSI11: JP35.1, R117.2
TARGET-MOSI12: JP38.1, R127.2
TARGET-MOSI13: JP41.1, R137.2
TARGET-MOSI14: JP44.1, R147.2
TARGET-MOSI15: JP47.1, R157.2
TARGET-MOSI16: JP50.1, R167.2
TARGET-MOSI17: JP53.1, R177.2
TARGET-MOSI18: JP56.1, R187.2
TARGET-MOSI19: JP59.1, R197.2
TARGET-MOSI20: JP62.1, R207.2
TARGET-MOSI21: JP65.1, R217.2
TARGET-MOSI22: JP68.1, R227.2
TARGET-MOSI23: JP71.1, R237.2
TARGET-MOSI24: JP74.1, R247.2
TARGET-MOSI25: JP77.1, R257.2
TARGET-MOSI26: JP80.1, R267.2
TARGET-MOSI27: JP83.1, R277.2
TARGET-MOSI28: JP86.1, R287.2
TARGET-MOSI29: JP89.1, R297.2
TARGET-MOSI30: JP92.1, R307.2
TARGET-MOSI31: JP95.1, R317.2
TARGET-PWR: JP3.2, R10.2, S1.2, U2.14
TARGET-PWR1: JP5.2, R20.2, S2.2, U4.14
TARGET-PWR2: JP8.2, R30.2, S3.2, U6.14
TARGET-PWR3: JP11.2, R40.2, S4.2, U8.14
TARGET-PWR4: JP14.2, R50.2, S5.2, U10.14
TARGET-PWR5: JP17.2, R60.2, S6.2, U12.14
TARGET-PWR6: JP20.2, R70.2, S7.2, U14.14
TARGET-PWR7: JP23.2, R80.2, S8.2, U16.14
TARGET-PWR8: JP26.2, R90.2, S9.2, U18.14
TARGET-PWR9: JP29.2, R100.2, S10.2, U20.14
TARGET-PWR10: JP32.2, R110.2, S11.2, U22.14
TARGET-PWR11: JP35.2, R120.2, S12.2, U24.14
TARGET-PWR12: JP38.2, R130.2, S13.2, U26.14
TARGET-PWR13: JP41.2, R140.2, S14.2, U28.14
TARGET-PWR14: JP44.2, R150.2, S15.2, U30.14
TARGET-PWR15: JP47.2, R160.2, S16.2, U32.14
TARGET-PWR16: JP50.2, R170.2, S17.2, U34.14
TARGET-PWR17: JP53.2, R180.2, S18.2, U36.14
TARGET-PWR18: JP56.2, R190.2, S19.2, U38.14
TARGET-PWR19: JP59.2, R200.2, S20.2, U40.14
TARGET-PWR20: JP62.2, R210.2, S21.2, U42.14
TARGET-PWR21: JP65.2, R220.2, S22.2, U44.14
TARGET-PWR22: JP68.2, R230.2, S23.2, U46.14
TARGET-PWR23: JP71.2, R240.2, S24.2, U48.14
TARGET-PWR24: JP74.2, R250.2, S25.2, U50.14
TARGET-PWR25: JP77.2, R260.2, S26.2, U52.14
TARGET-PWR26: JP80.2, R270.2, S27.2, U54.14
TARGET-PWR27: JP83.2, R280.2, S28.2, U56.14
TARGET-PWR28: JP86.2, R290.2, S29.2, U58.14
TARGET-PWR29: JP89.2, R300.2, S30.2, U60.14
TARGET-PWR30: JP92.2, R310.2, S31.2, U62.14
TARGET-PWR31: JP95.2, R320.2, S32.2, U64.14
TARGET-RST: JP3.5, U2.3
TARGET-RST1: JP5.5, U4.3
TARGET-RST2: JP8.5, U6.3
TARGET-RST3: JP11.5, U8.3
TARGET-RST4: JP14.5, U10.3
TARGET-RST5: JP17.5, U12.3
TARGET-RST6: JP20.5, U14.3
TARGET-RST7: JP23.5, U16.3
TARGET-RST8: JP26.5, U18.3
TARGET-RST9: JP29.5, U20.3
TARGET-RST10: JP32.5, U22.3
TARGET-RST11: JP35.5, U24.3
TARGET-RST12: JP38.5, U26.3
TARGET-RST13: JP41.5, U28.3
TARGET-RST14: JP44.5, U30.3
TARGET-RST15: JP47.5, U32.3
TARGET-RST16: JP50.5, U34.3
TARGET-RST17: JP53.5, U36.3
TARGET-RST18: JP56.5, U38.3
TARGET-RST19: JP59.5, U40.3
TARGET-RST20: JP62.5, U42.3
TARGET-RST21: JP65.5, U44.3
TARGET-RST22: JP68.5, U46.3
TARGET-RST23: JP71.5, U48.3
TARGET-RST24: JP74.5, U50.3
TARGET-RST25: JP77.5, U52.3
TARGET-RST26: JP80.5, U54.3
TARGET-RST27: JP83.5, U56.3
TARGET-RST28: JP86.5, U58.3
TARGET-RST29: JP89.5, U60.3
TARGET-RST30: JP92.5, U62.3
TARGET-RST31: JP95.5, U64.3
TARGET-SCK: JP3.7, R8.2
TARGET-SCK1: JP5.7, R18.2
TARGET-SCK2: JP8.7, R28.2
TARGET-SCK3: JP11.7, R38.2
TARGET-SCK4: JP14.7, R48.2
TARGET-SCK5: JP17.7, R58.2
TARGET-SCK6: JP20.7, R68.2
TARGET-SCK7: JP23.7, R78.2
TARGET-SCK8: JP26.7, R88.2
TARGET-SCK9: JP29.7, R98.2
TARGET-SCK10: JP32.7, R108.2
TARGET-SCK11: JP35.7, R118.2
TARGET-SCK12: JP38.7, R128.2
TARGET-SCK13: JP41.7, R138.2
TARGET-SCK14: JP44.7, R148.2
TARGET-SCK15: JP47.7, R158.2
TARGET-SCK16: JP50.7, R168.2
TARGET-SCK17: JP53.7, R178.2
TARGET-SCK18: JP56.7, R188.2
TARGET-SCK19: JP59.7, R198.2
TARGET-SCK20: JP62.7, R208.2
TARGET-SCK21: JP65.7, R218.2
TARGET-SCK22: JP68.7, R228.2
TARGET-SCK23: JP71.7, R238.2
TARGET-SCK24: JP74.7, R248.2
TARGET-SCK25: JP77.7, R258.2
TARGET-SCK26: JP80.7, R268.2
TARGET-SCK27: JP83.7, R278.2
TARGET-SCK28: JP86.7, R288.2
TARGET-SCK29: JP89.7, R298.2
TARGET-SCK30: JP92.7, R308.2
TARGET-SCK31: JP95.7, R318.2
VCC: C1.A, C2.1, D3.A, F1.2, JP1.1, JP1.2, JP2.2, R6.2, S1.1, U1.20
VCC1: C5.1, C6.A, D6.A, F2.2, JP4.1, JP4.2, JP6.2, R16.2, S2.1, U3.20
VCC2: C9.1, C10.A, D9.A, F3.2, JP7.1, JP7.2, JP9.2, R26.2, S3.1, U5.20
VCC3: C13.1, C14.A, D12.A, F4.2, JP10.1, JP10.2, JP12.2, R36.2, S4.1, U7.20
VCC4: C17.1, C18.A, D15.A, F5.2, JP13.1, JP13.2, JP15.2, R46.2, S5.1, U9.20
VCC5: C21.1, C22.A, D18.A, F6.2, JP16.1, JP16.2, JP18.2, R56.2, S6.1, U11.20
VCC6: C25.1, C26.A, D21.A, F7.2, JP19.1, JP19.2, JP21.2, R66.2, S7.1, U13.20
VCC7: C29.1, C30.A, D24.A, F8.2, JP22.1, JP22.2, JP24.2, R76.2, S8.1, U15.20
VCC8: C33.1, C34.A, D27.A, F9.2, JP25.1, JP25.2, JP27.2, R86.2, S9.1, U17.20
VCC9: C37.1, C38.A, D30.A, F10.2, JP28.1, JP28.2, JP30.2, R96.2, S10.1, U19.20
VCC10: C41.1, C42.A, D33.A, F11.2, JP31.1, JP31.2, JP33.2, R106.2, S11.1, U21.20
VCC11: C45.1, C46.A, D36.A, F12.2, JP34.1, JP34.2, JP36.2, R116.2, S12.1, U23.20
VCC12: C49.1, C50.A, D39.A, F13.2, JP37.1, JP37.2, JP39.2, R126.2, S13.1, U25.20
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
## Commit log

2013-04-22 Adding driver, firmware and hardware files.
2013-04-22 Update README.md
    Fixed typo in name.
2013-10-07 Adding Zadig to drivers folder for easier installation on Windows 8
2013-12-03 QC Revision
    1.) 0402 to 0603 footprints
    2.) OSHW logo
    3.) Switch date code to rev code
    Will be adding new PTC footprint soon
2013-12-04 QC Revision - second round
    In addition to the three previous changes:
    1.) Updated PTC footprint
    2.) General schematic cleanup
    3.) OSHW and Creative Commons info
2014-01-15 Created Giant and Regular Panels
2014-05-11 Added Case STL Files
    These STL files can be 3d printed, and provide some protection for the
    programmer.
2014-05-13 Modifying repo structure and updating README.
2014-08-23 Updated usbtiny drivers to version 1.2.6.0
2014-08-23 Updated Zadig USB driver installer to version 2.1.0.658
2014-08-23 Updated to usbtiny 1.7
2015-08-27 Replaced old drivers with the newer signed version
2016-01-04 re-created panel v11, more strength
2025-06-27 Update README.md
    Updating link.
